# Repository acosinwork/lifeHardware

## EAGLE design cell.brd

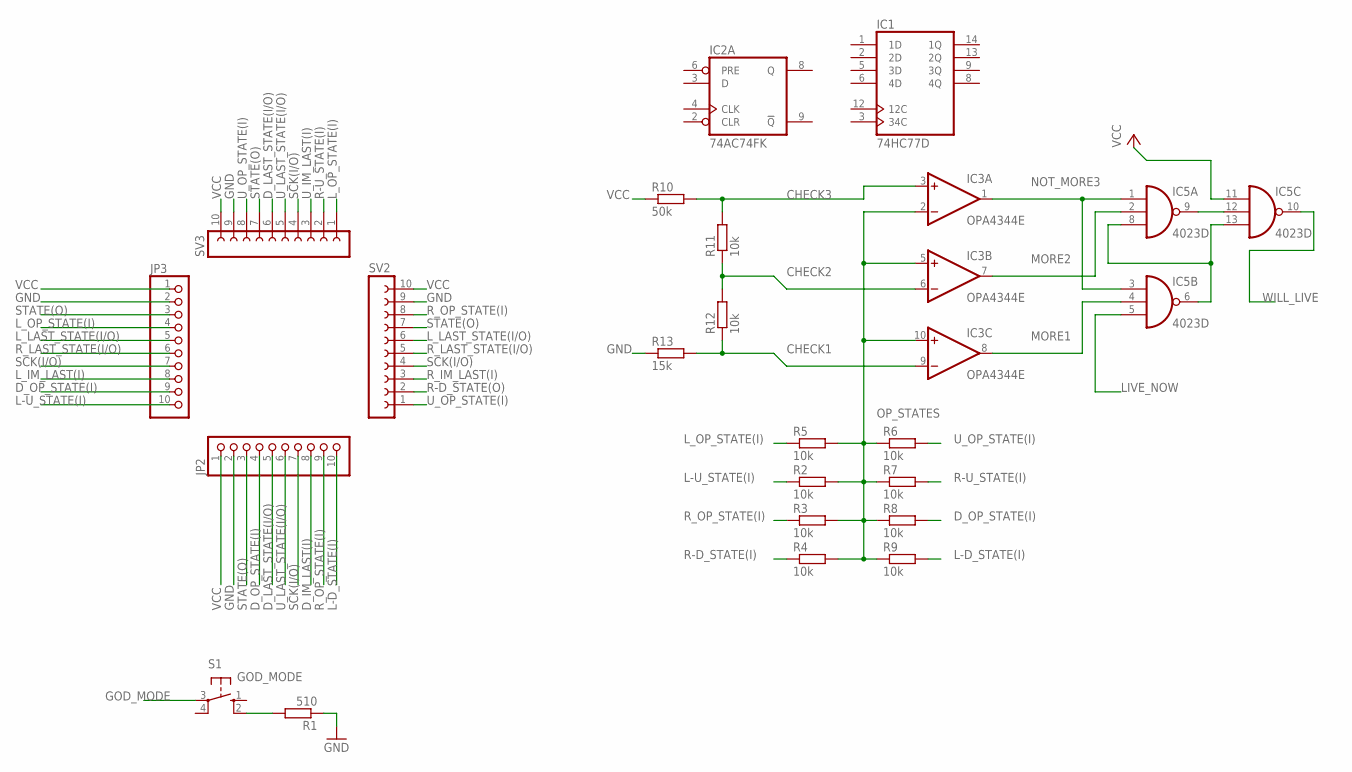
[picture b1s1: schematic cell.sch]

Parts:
IC1: 74HC77D; SO14
IC2: 74AC74FK; LCC20
IC3: OPA4344E; TSSOP14
IC5: 4023D; SO14
JP2, JP3: PINHD-1X10; 1X10
R1: 510; R0805
R2, R3, R4, R5, R6, R7, R8, R9, R11, R12: 10k; R0805
R10: 50k; R0805
R13: 15k; R0805
S1: GOD_MODE; B3F-10XX
SV2, SV3: FE10W

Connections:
CHECK1: IC3.9 (-IN), R12.1, R13.2
CHECK2: IC3.6 (-IN), R11.1, R12.2
CHECK3: IC3.3 (+IN), R10.2, R11.2
D_IM_LAST(I): JP2.8
D_LAST_STATE(I/O): JP2.5, SV3.6
D_OP_STATE(I): JP2.4, JP3.9, R8.2
GND: IC1.11 (GND), IC2.10 (GND), JP2.2, JP3.2, R1.1, R13.1, SV2.9, SV3.9
GOD_MODE: S1.3
L-D_STATE(I): JP2.10, R9.2
L-U_STATE(I): JP3.10, R2.1
LIVE_NOW: IC5.5 (I2)
L_IM_LAST(I): JP3.8
L_LAST_STATE(I/O): JP3.5, SV2.6
L_OP_STATE(I): JP3.4, R5.1, SV3.1
MORE1: IC3.8 (OUT), IC5.4 (I1)
MORE2: IC3.7 (OUT), IC5.2 (I1)
unnamed: R1.2, S1.2 (S1)
unnamed: IC5.6 (O), IC5.8 (I2), IC5.13 (I2)
unnamed: IC5.9 (O), IC5.12 (I1)
NOT_MORE3: IC3.1 (OUT), IC5.1 (I0), IC5.3 (I0)
OP_STATES: IC3.2 (-IN), IC3.5 (+IN), IC3.10 (+IN), R2.2, R3.2, R4.2, R5.2, R6.1, R7.1, R8.1, R9.1
R-D_STATE(I): R4.1
R-D_STATE(O): SV2.2
R-U_STATE(I): R7.2, SV3.2
R_IM_LAST(I): SV2.3
R_LAST_STATE(I/O): JP3.6, SV2.5
R_OP_STATE(I): JP2.9, R3.1, SV2.8
SCK(I/O): JP2.7, JP3.7, SV2.4, SV3.4
STATE(O): JP2.3, JP3.3, SV2.7, SV3.7
U_IM_LAST(I): SV3.3
U_LAST_STATE(I/O): JP2.6, SV3.5
U_OP_STATE(I): R6.2, SV2.1, SV3.8
V+: IC3.4 (V+)
V-: IC3.11 (V-)
VCC: IC1.4 (VCC), IC2.20 (VCC), IC5.11 (I0), JP2.1, JP3.1, R10.1, SV2.10, SV3.10
VDD: IC5.14 (VDD)
VSS: IC5.7 (VSS)
WILL_LIVE: IC5.10 (O)

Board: 2 copper layers, 22 parts (0 on the bottom side), 25 nets, no tracks yet.
